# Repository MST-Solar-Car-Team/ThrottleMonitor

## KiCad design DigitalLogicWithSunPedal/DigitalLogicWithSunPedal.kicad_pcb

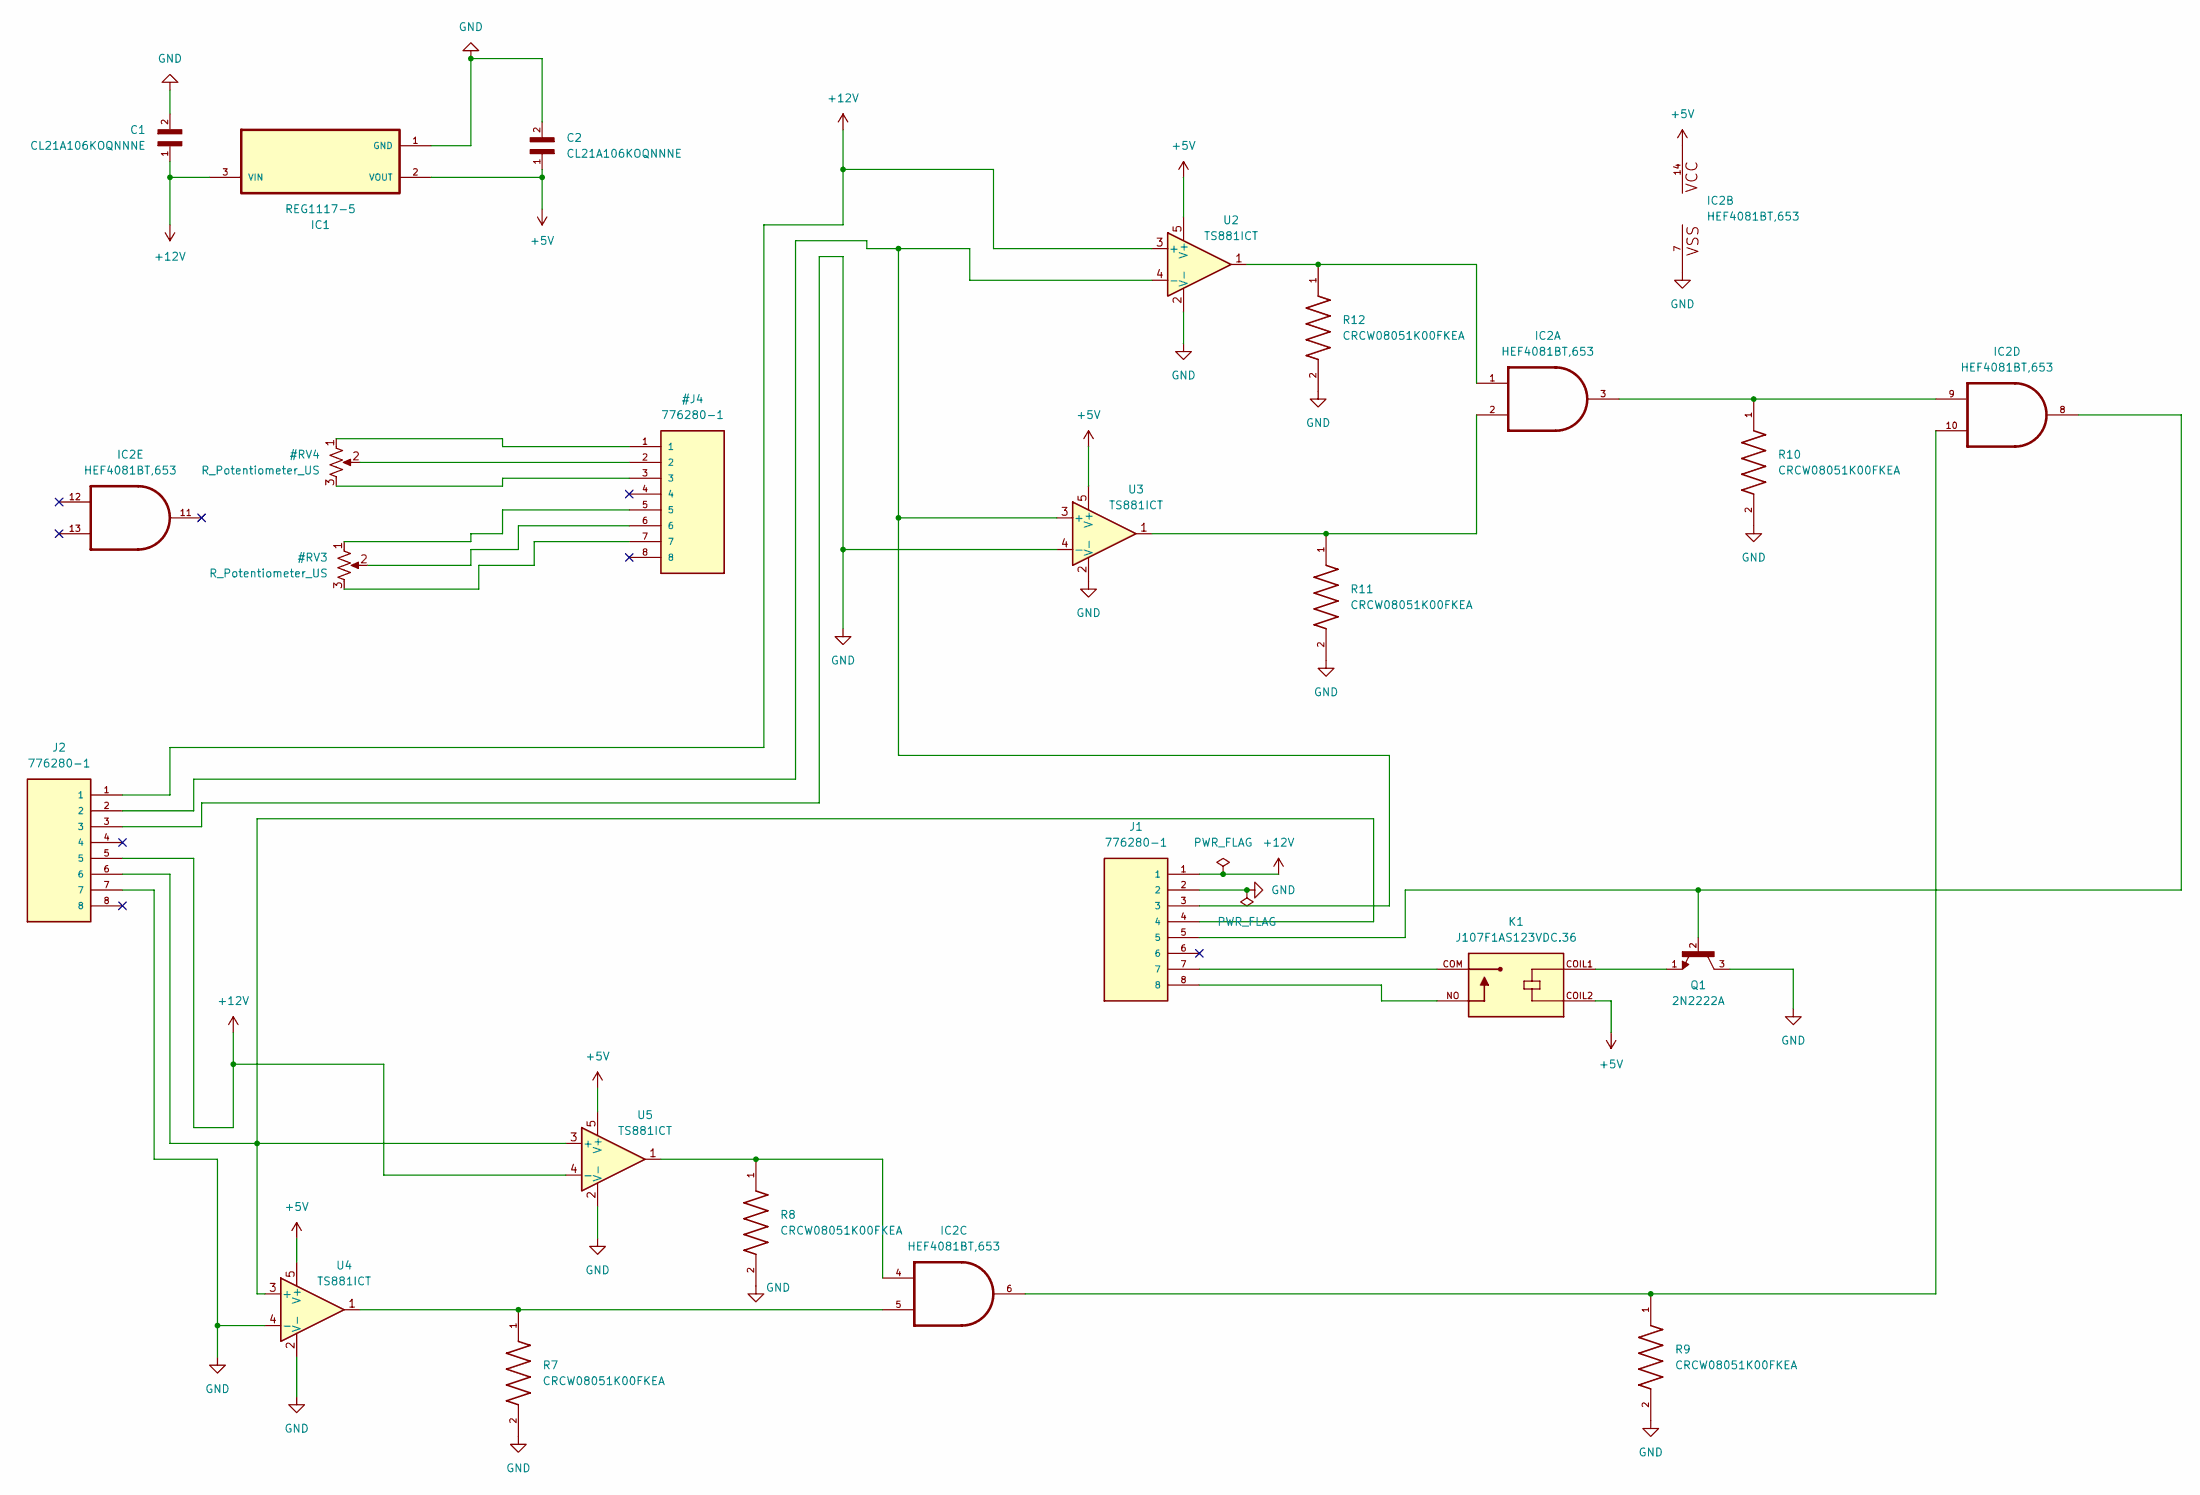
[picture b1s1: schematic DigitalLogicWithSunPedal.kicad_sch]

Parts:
C1, C2: CL21A106KOQNNNE; CAPC2012X140N
IC1: REG1117-5; SOT230P700X180-4N
IC2: HEF4081BT,653; SOIC-14_3.9x8.7mm_P1.27mm
J1, J2: 776280-1; TE_776280-1; PARTREV F8
K1: J107F1AS123VDC.36; RELAY_J107F1AS123VDC.36; PARTREV B; DigiKey_Part_Number 2449-J107F1AS123VDC.36-ND
Q1: 2N2222A; TO92254P470H750-3; PARTREV N/A
R7, R8, R9, R10, R11, R12: CRCW08051K00FKEA; RESC2012X50N
U2, U3, U4, U5: TS881ICT; SOT-353_SC-70-5

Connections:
+5V: C2.1, IC1.2 (VOUT), IC2.14, K1.COIL2, U2.5 (V+), U3.5 (V+), U4.5 (V+), U5.5 (V+)
+12V: C1.1, IC1.3 (VIN), J1.1, J2.1, J2.5, U2.3 (+), U5.4 (-)
GND: C1.2, C2.2, IC1.1 (GND), IC2.7, J1.2, J2.3, J2.7, Q1.3, R7.2, R8.2, R9.2, R10.2, R11.2, R12.2, U2.2 (V-), U3.2 (V-), U3.4 (-), U4.2 (V-), U4.4 (-), U5.2 (V-)
unnamed: IC2.1, R12.1, U2.1
unnamed: IC2.2, R11.1, U3.1
unnamed: IC2.3, IC2.9, R10.1
unnamed: IC2.4, R8.1, U5.1
unnamed: IC2.5, R7.1, U4.1
unnamed: IC2.8, J1.5, Q1.2
unnamed: IC2.6, IC2.10, R9.1
unnamed: J1.7, K1.COM
unnamed: J1.8, K1.NO
unnamed: K1.COIL1, Q1.1
unnamed: J1.3, J2.2, U2.4 (-), U3.3 (+)
unnamed: J1.4, J2.6, U4.3 (+), U5.3 (+)

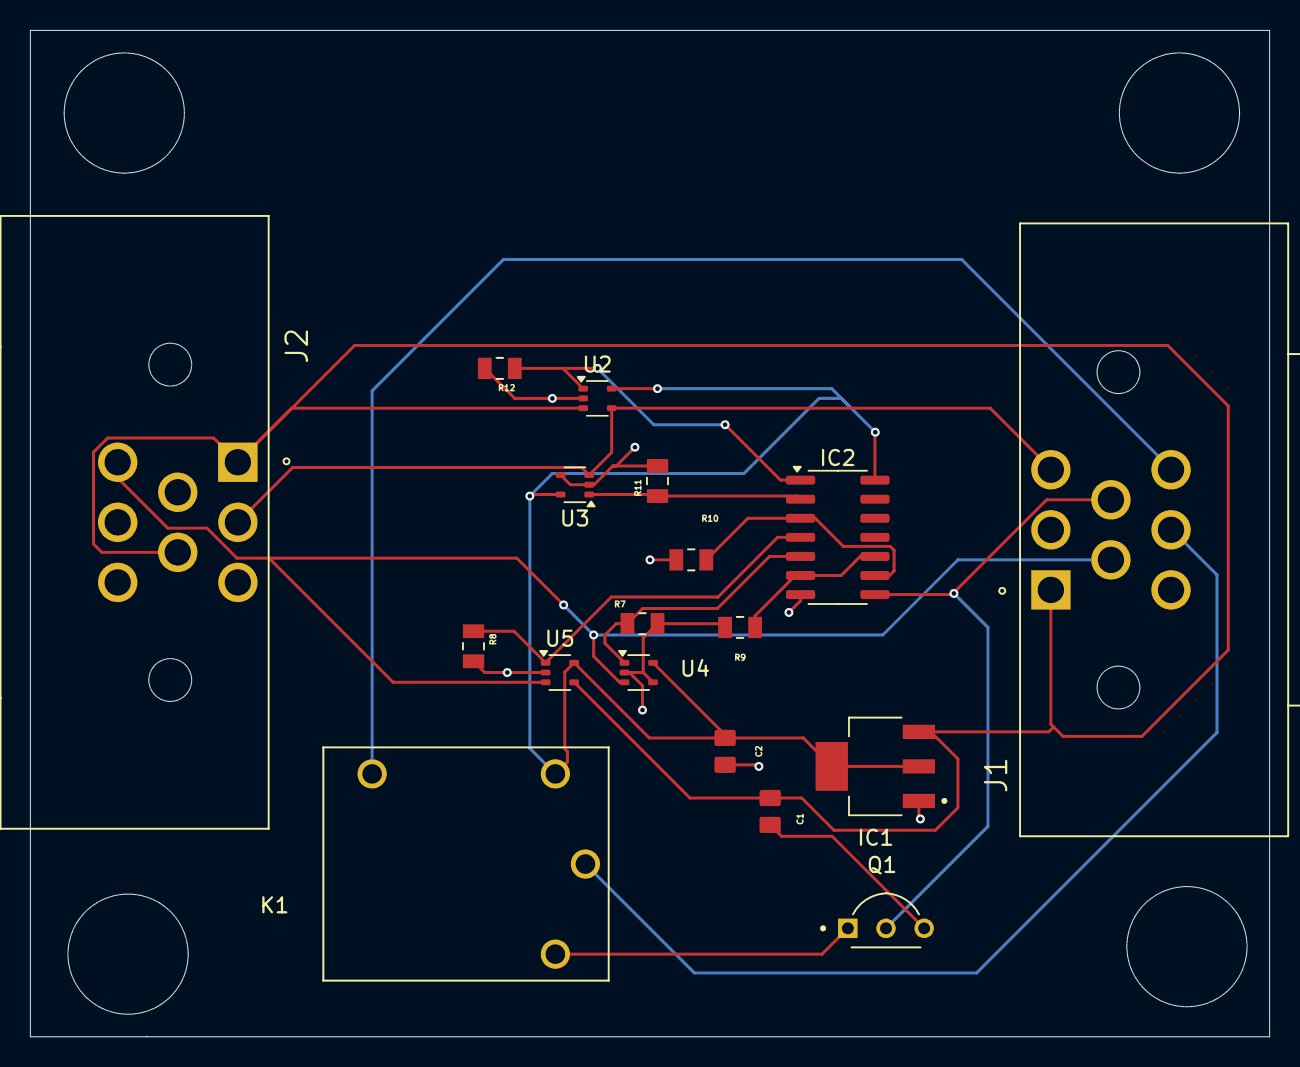
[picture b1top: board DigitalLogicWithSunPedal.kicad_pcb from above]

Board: 2 copper layers, 82.5 x 67.0 mm, 18 parts (0 on the bottom side), 15 nets.
